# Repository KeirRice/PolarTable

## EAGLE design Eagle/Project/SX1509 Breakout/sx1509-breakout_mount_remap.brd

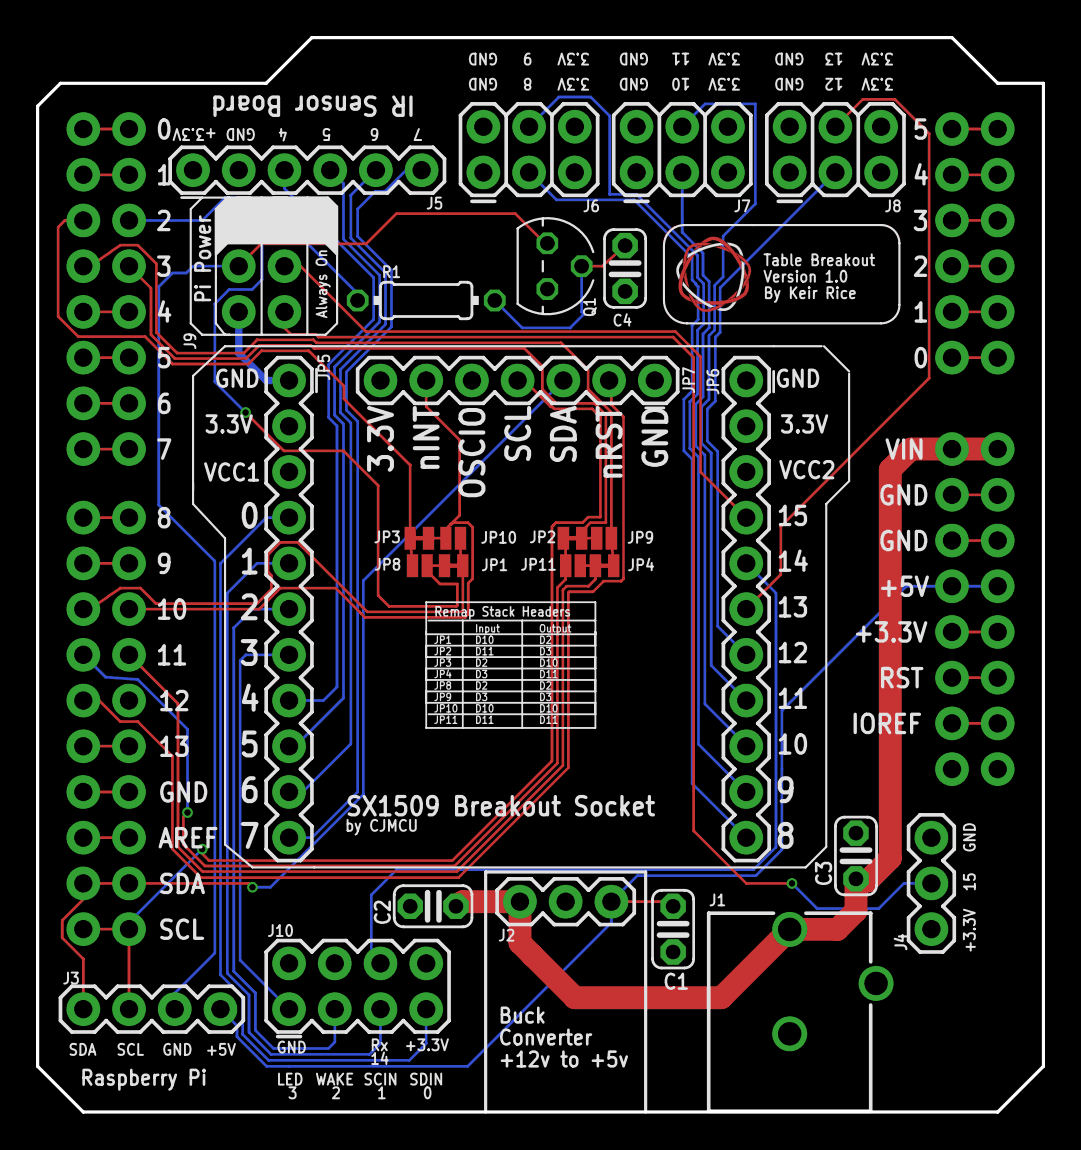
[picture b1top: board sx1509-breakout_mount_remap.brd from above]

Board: 2 copper layers, 55.9 x 59.7 mm, 30 parts (0 on the bottom side), 56 nets.

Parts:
B1: DownConnection; UNO_R3_SHIELD_NOLABELS
B2: UpConnection; UNO_R3_SHIELD_NOLABELS
C1, C2, C3, C4: 0.1uF; C025-024X044
J1: Pi Power Jack; POWER_JACK_PTH_BREAD
J2: 12V to 5V; 1X03
J3: Pi Connection; 1X04
J4: 1X03
J5: IR Sensors; 1X06
J6: Switch A + B; 2X3
J7: Switch C + D; 2X3
J8: Switch E + F; 2X3
J9: 2X3-NS
J10: LED + Radio; 2X4
JP1, JP2, JP3, JP4: SMT-JUMPER_2_NC_TRACE_NO-SILK
JP5, JP6: 1X11
JP7: 1X07
JP8, JP9, JP10, JP11: SMT-JUMPER_2_NO_NO-SILK
Q1: BC337; TO92
R1: 100; 0204/7
U$1: TRI_LOGO_5MM

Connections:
3.3V: B1.3.3V, B2.3.3V, J4.1, J5.1, J6.5, J6.6, J7.5, J7.6, J8.5, J8.6, J10.8, JP5.2, JP6.2, JP7.7
4: J5.3, JP5.8
5: J5.4, JP5.9
5V: B1.5V, B2.5V, C1.1, J2.3, J3.1
6: J5.5, JP5.10
7: J5.6, JP5.11
8: J6.3, JP6.11
9: J6.4, JP6.10
10: J7.3, JP6.9
11: J7.4, JP6.8
12: J8.3, JP6.7
12V: B1.VIN, B2.VIN, C2.2, C3.1, J1.PWR, J2.1
13: J8.4, JP6.6
15: J9.4, JP6.4
*D5: B1.D5, B2.D5
*D6: B1.D6, B2.D6
*D9: B1.D9, B2.D9
A0: B1.A0, B2.A0
A1: B1.A1, B2.A1
A2: B1.A2, B2.A2
A3: B1.A3, B2.A3
A4: B1.A4, B2.A4
A5: B1.A5, B2.A5
AREF: B1.AREF, B2.AREF
D4: B1.D4, B2.D4
D7: B1.D7, B2.D7
D8: B1.D8, B2.D8
D13: B1.D13, B2.D13
GND: C1.2, C2.1, C3.2, C4.2, J1.GND, J1.GNDBREAK, J2.2, J4.3, J5.2, J6.1, J6.2, J7.1, J7.2, J8.1, J8.2, J9.5, J10.2, JP5.1, JP6.1, JP7.1, Q1.1
GND@0: B1.GND@0, B2.GND@0
GND@1: B1.GND@1, B2.GND@1
GND@2: B1.GND@2, B2.GND@2
IOREF: B1.IOREF, B2.IOREF
unnamed: C4.1, Q1.2, R1.2
unnamed: J4.2, J9.6
unnamed: J9.2, R1.1
unnamed: B1.D2, JP3.2, JP8.2
unnamed: B1.D3, JP4.2, JP9.2
unnamed: B1.D10, JP1.2, JP10.2
unnamed: B1.D11, JP2.2, JP11.2
unnamed: B2.D2, JP1.1, JP8.1
unnamed: B2.D3, JP2.1, JP9.1
unnamed: B2.D11, JP4.1, JP11.1
NINT: B2.D10, JP3.1, JP7.6, JP10.1
NRESET: B1.D12, JP7.2
PI_GROUND: J3.2, J9.3, Q1.3
RES: B1.RES, B2.RES
RX: B1.RX, B2.RX
RXDATA: J10.6, JP6.5
SCIN: J10.5, JP5.5
SCL: B1.SCL, B2.SCL, J3.3, JP7.4
SDA: B1.SDA, B2.SDA, J3.4, JP7.3
SDIN: J10.7, JP5.4
TX: B1.TX, B2.TX
WAKE_LED: J10.1, JP5.7
WAKE_SW: J10.3, JP5.6

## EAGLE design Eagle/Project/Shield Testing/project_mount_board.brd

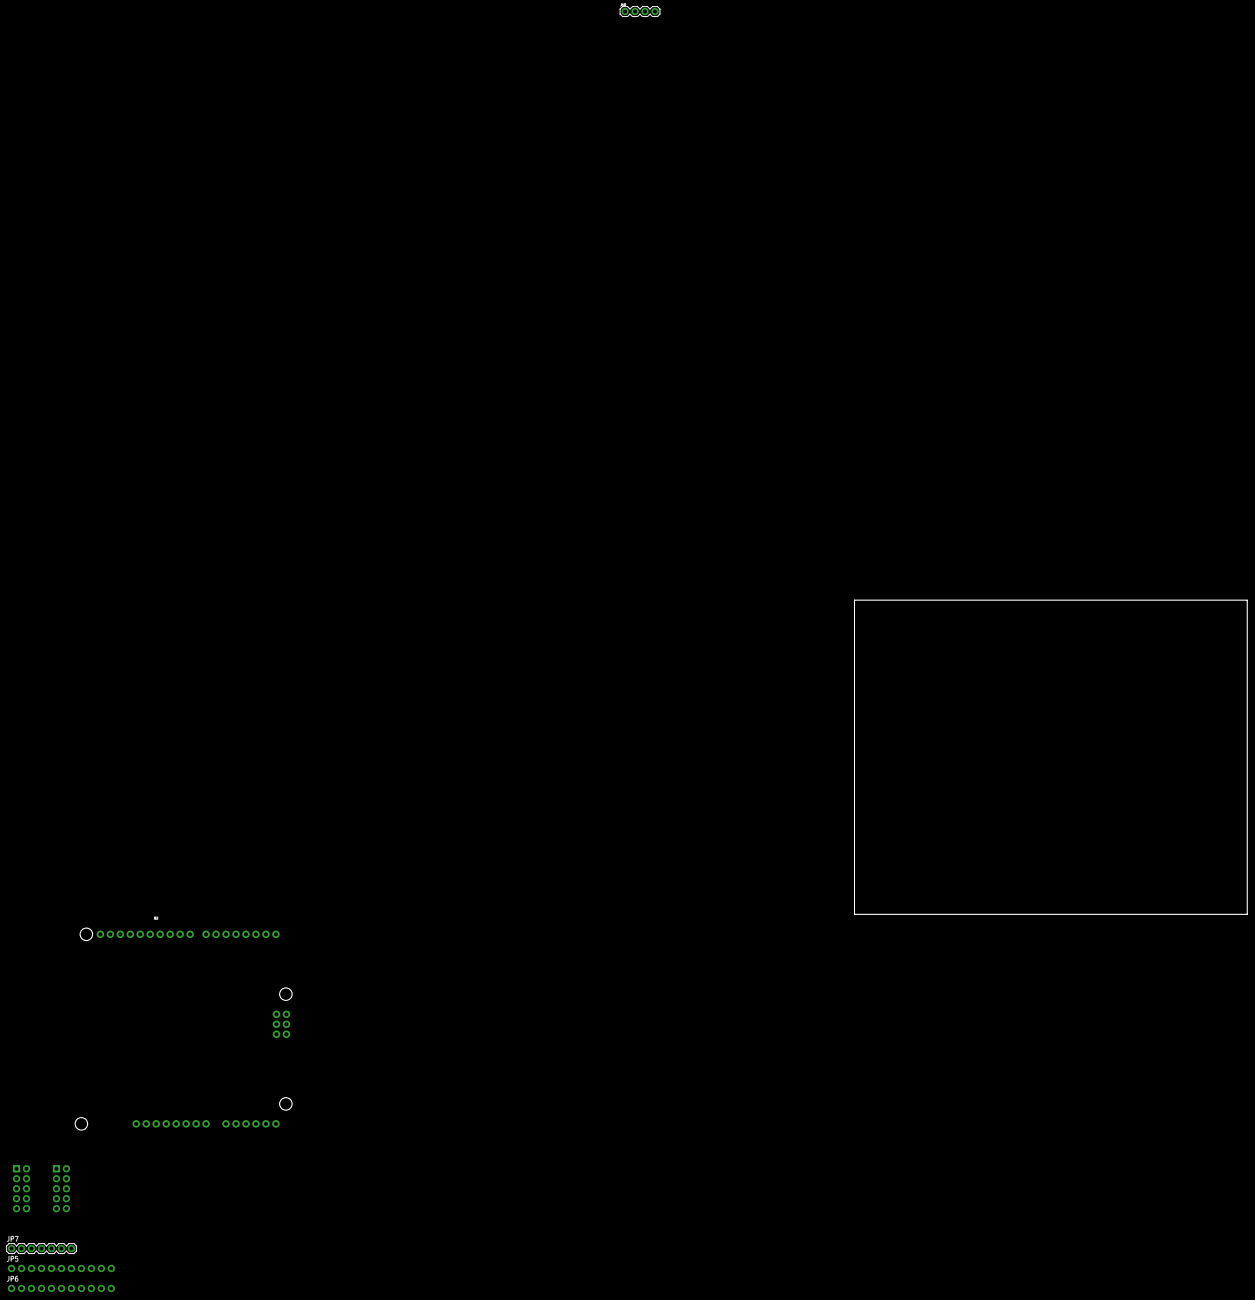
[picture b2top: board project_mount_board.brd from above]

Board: 2 copper layers, 100.0 x 80.0 mm, 7 parts (0 on the bottom side), 3 nets, no tracks yet.

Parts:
B2: ARDUINO_UNO_R3; ARDUINO_R3
J10: 1X04
JP1: IDC-5X2; 2X5-SHROUDED-NO_SILK
JP2: IDC-5x2; 2X5-SHROUDED-NO_SILK
JP5, JP6: 1X11_NO_SILK
JP7: 1X07

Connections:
5V: B2.5V, J10.4
GND: B2.GND@1, B2.GND@2, B2.GND@3, B2.GND@4, J10.1
RXDATA: B2.D12, J10.2

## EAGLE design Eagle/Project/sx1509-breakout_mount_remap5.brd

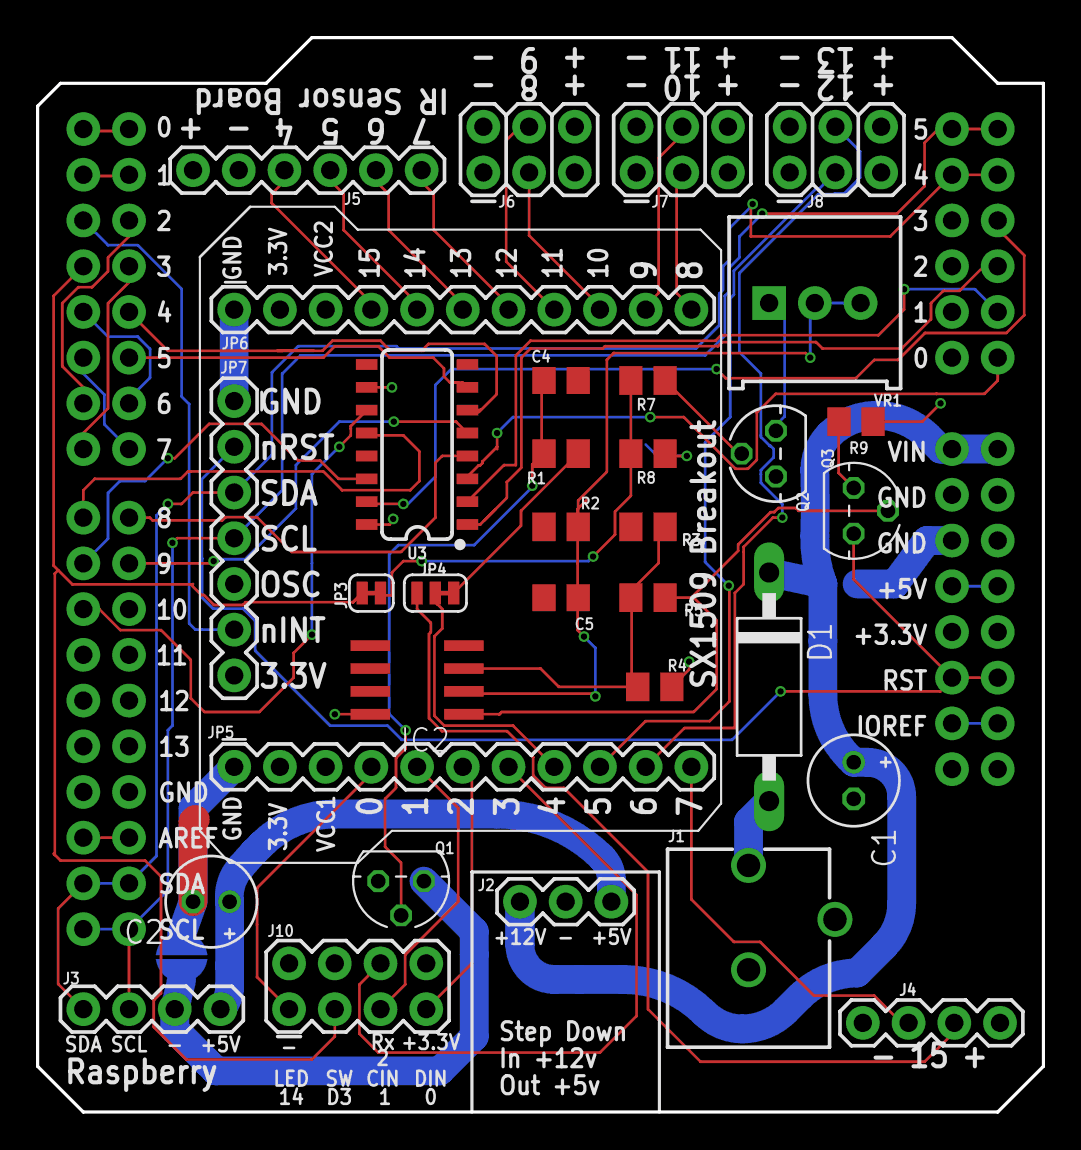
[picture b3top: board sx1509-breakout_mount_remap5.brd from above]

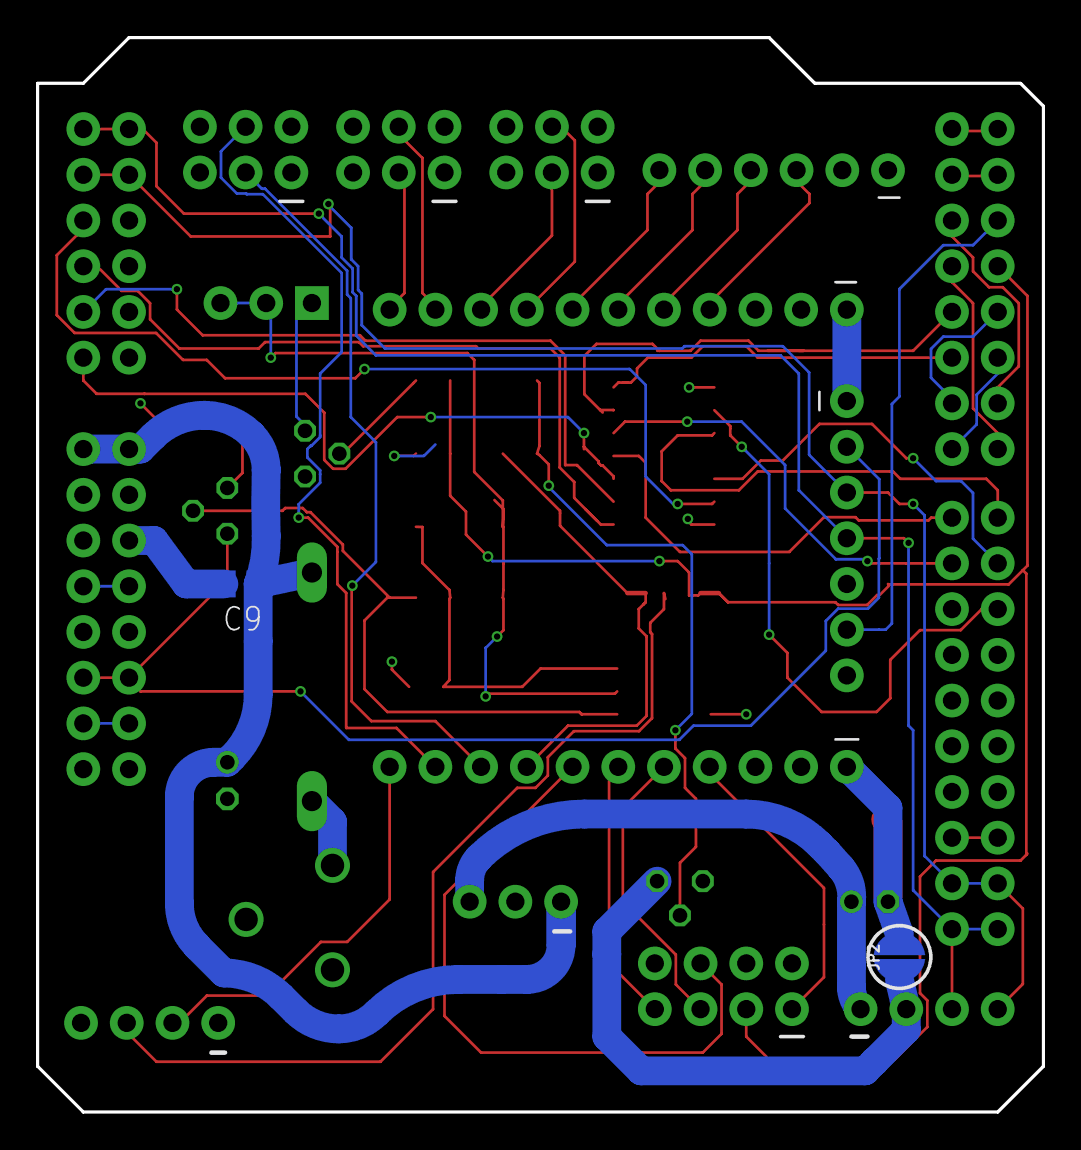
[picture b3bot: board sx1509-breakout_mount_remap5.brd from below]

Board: 2 copper layers, 55.9 x 59.7 mm, 38 parts (2 on the bottom side), 57 nets.

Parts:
B1: Connect down to Arduino; UNO_R3_SHIELD_NOLABELS
B2: Connect up to motor shield; UNO_R3_SHIELD_NOLABELS
C1, C2: 100u; E2-5
C4: 100nF; C0805
C5: 330uF; C0805
C9: 100n; C0805
D1: 1N5408; DO15-12
IC2: LM358D; SO08
J1: Pi Power Jack; POWER_JACK_PTH_BREAD
J2: Header - Right angled, female; 1X03
J3: Pi Connection; 1X04_1.24MM_RA_MALE
J4: extra points; 1X04_1.24MM_RA_MALE
J5: IR Sensors; 1X06
J6: Switch A + B; 2X3
J7: Switch C + D; 2X3
J8: Switch E + F; 2X3
J10: LED + Radio; 2X4
JP2: Bypass Power Control; SMT-JUMPER_2_NO_SILK_ROUND
JP3: Enable Hold to Reset; SMT-JUMPER_2_NC_TRACE_SILK
JP4: Route 15 to external; SMT-JUMPER_3_1-NC_TRACE_SILK
JP5: Left Sub-board Mount; 1X11
JP6: Right Sub-board Mount; 1X11
JP7: Top Sub-board Mount; 1X07
Q1: BC337; TO92
Q2: 2N3906; TO92D
Q3: BC547; TO92
R1, R7, R8, R9: 1k; M0805
R2: 22.1k; M0805
R3: 22k; M0805
R4: 16.2k; M0805
R5: 221k; M0805
U3: SN74HC595DR; SO16
U$2: TRI_LOGO_TOP_15MM
VR1: 10k; TRIMPOT-PTH-3386U

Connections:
3.3V: B1.3.3V, B2.3.3V, IC2.8, J4.1, J5.1, J6.5, J6.6, J7.5, J7.6, J8.5, J8.6, J10.8, JP5.2, JP6.2, JP7.7, Q2.E, R4.2, R8.1, R9.1, U3.10, U3.16
5V: B1.5V, B2.5V
12V: B1.VIN, B2.VIN, C1.+, C9.1, D1.C, J2.1
15_PLUG: J4.2, JP4.1
$N99: JP3.2, R7.2, R8.2
AREF: B1.AREF, B2.AREF
B0: J10.1, JP5.4
B1_SCIN: J10.5, JP5.5
B2_SDIN: J10.7, JP5.6
B3_RXDATA: J10.6, JP5.7
B4: JP4.2, JP5.8
B5: J8.3, JP5.9
B6: J8.4, JP5.10
B7: J4.3, JP5.11
B8: J7.3, JP6.11
B9: J7.4, JP6.10
B10: J6.3, JP6.9
B11: J6.4, JP6.8
B12: J5.6, JP6.7
B13: J5.5, JP6.6
B14: J5.4, JP6.5
B15: J5.3, JP6.4
CLK: B1.D10, U3.11
COMP_OUT: IC2.1, Q3.2, R5.1
DATA: B1.D9, U3.14
ENX: B2.A2, U3.1
ENY: B2.A0, U3.3
GND: B1.GND@0, B1.GND@1, B1.GND@2, B2.GND@0, B2.GND@1, B2.GND@2, C1.-, C2.-, C4.2, C5.2, C9.2, IC2.4, J1.GND, J1.GNDBREAK, J2.2, J4.4, J5.2, J6.1, J6.2, J7.1, J7.2, J8.1, J8.2, J10.2, JP2.2, JP5.1, JP6.1, JP7.1, Q1.1, R2.1, R3.1, U3.8, U3.13
IOREF: B1.IOREF, B2.IOREF
LATCH: B1.D8, U3.12
unnamed: Q2.B, R7.1
unnamed: C4.1, Q1.2, R1.2
unnamed: Q3.3, R9.2
unnamed: D1.A, J1.PWR
unnamed: IC2.3, R3.2, R4.1, R5.2
unnamed: Q2.C, VR1.1
unnamed: C5.1, IC2.2, R2.2, VR1.2, VR1.3
NINT: B1.D2, JP7.6
PIPOWER_SIGNAL: JP4.3, R1.1
PI_5V: C2.+, J2.3, J3.1
PI_GROUND: J3.2, JP2.1, Q1.3
RES: B1.RES, B2.RES, JP7.2, Q3.1
RX: B1.RX, B2.RX
SCL: B1.A5, B1.SCL, B2.A5, B2.SCL, J3.3, JP7.4
SDA: B1.A4, B1.SDA, B2.A4, B2.SDA, J3.4, JP7.3
SLEEPX: B2.A3, U3.15
SLEEPY: B2.A1, U3.2
TX: B1.TX, B2.TX
WAKE_SW: B1.D3, J10.3, JP3.1
XDIR: B1.D7, B2.D3
XMS1: B2.D4, U3.6
XMS2: B2.D5, U3.7
XSTEP: B1.D6, B2.D2
YDIR: B1.D5, B2.D7
YMS1: B2.D8, U3.4
YMS2: B2.D9, U3.5
YSTEP: B1.D4, B2.D6

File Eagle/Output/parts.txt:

Partlist

Exported from sx1509-breakout_mount_remap5.sch at 9/27/2018 1:54 PM

EAGLE Version 9.1.3 Copyright (c) 1988-2018 Autodesk, Inc.

Assembly variant: 

Part     Value                         Device                         Package                      Library                 Sheet

B1       Connect down to Arduino       ARDUINO_UNO_R3_SHIELDNOLABELS  UNO_R3_SHIELD_NOLABELS       keir_library            1
B2       Connect up to motor shield    ARDUINO_UNO_R3_SHIELDNOLABELS  UNO_R3_SHIELD_NOLABELS       keir_library            1
C1       100u                          CPOL-EUE2-5                    E2-5                         rcl                     1
C2       100u                          CPOL-EUE2-5                    E2-5                         rcl                     1
C4       100nF                         C-EUC0805                      C0805                        resistor                1
C5       330uF                         C-EUC0805                      C0805                        resistor                1
C9       100n                          C-EUC0805                      C0805                        rcl                     1
D1       1N5408                        1N5408                         DO15-12                      keir_library            1
IC2      LM358D                        LM358D                         SO08                         keir_library            1
J1       Pi Power Jack                 POWER_JACKPTH_BREAD            POWER_JACK_PTH_BREAD         SparkFun-Connectors     1
J2       Header - Right angled, female CONN_031X03_2.54MM_RA_FEMALE   1X03                         keir_library            1
J3       Pi Connection                 CONN_041X04_1.24MM_RA_MALE     1X04_1.24MM_RA_MALE          keir_library            1
J4                                     CONN_041X04_1.24MM_RA_MALE     1X04_1.24MM_RA_MALE          keir_library            1
J5       IR Sensors                    CONN_06SILK_FEMALE_PTH         1X06                         SparkFun-Connectors     1
J6       Switch A + B                  CONN_03X22X03_2.54MM_RA_MALE   2X3                          keir_library            1
J7       Switch C + D                  CONN_03X22X03_2.54MM_RA_MALE   2X3                          keir_library            1
J8       Switch E + F                  CONN_03X22X03_2.54MM_RA_MALE   2X3                          keir_library            1
J10      LED + Radio                   CONN_04X22X4_1.24MM_RA_MALE    2X4                          keir_library            1
JP2      Bypass Power Control          JUMPER-SMT_2_NO_SILK_ROUND     SMT-JUMPER_2_NO_SILK_ROUND   SparkFun-Jumpers        1
JP3      Enable Hold to Reset          JUMPER-SMT_2_NC_TRACE_SILK     SMT-JUMPER_2_NC_TRACE_SILK   SparkFun-Jumpers        1
JP4      Route 15 to external          JUMPER-SMT_3_1-NC_TRACE_SILK   SMT-JUMPER_3_1-NC_TRACE_SILK SparkFun-Jumpers        1
JP5                                    CONN_11                        1X11                         SparkFun-Connectors     1
JP6                                    CONN_11                        1X11                         SparkFun-Connectors     1
JP7                                    M07                            1X07                         SparkFun-Connectors     1
Q1       BC337                         BC337                          TO92                         transistor-npn          1
Q2       2N3906                        2N3906                         TO92D                        transistor-small-signal 1
Q3       BC547                         BC547                          TO92                         transistor-npn          1
R1       100                           R-US_R0805                     R0805                        resistor                1
R2       22.1k                         R-US_R0805                     R0805                        resistor                1
R3       22k                           R-US_R0805                     R0805                        resistor                1
R4       16.2k                         R-US_R0805                     R0805                        resistor                1
R5       221k                          R-US_R0805                     R0805                        resistor                1
R7       1k                            R-US_R0805                     R0805                        resistor                1
R8       1k                            R-US_R0805                     R0805                        resistor                1
R9       1k                            R-US_R0805                     R0805                        resistor                1
U3       SN74HC595DR                   SN74HC595HCD                   SO16                         keir_library            1
VR1      10k                           TRIMPOT-PTH-10MM-KNOB-1/2W-10% TRIMPOT-PTH-3386U            SparkFun-Resistors      1

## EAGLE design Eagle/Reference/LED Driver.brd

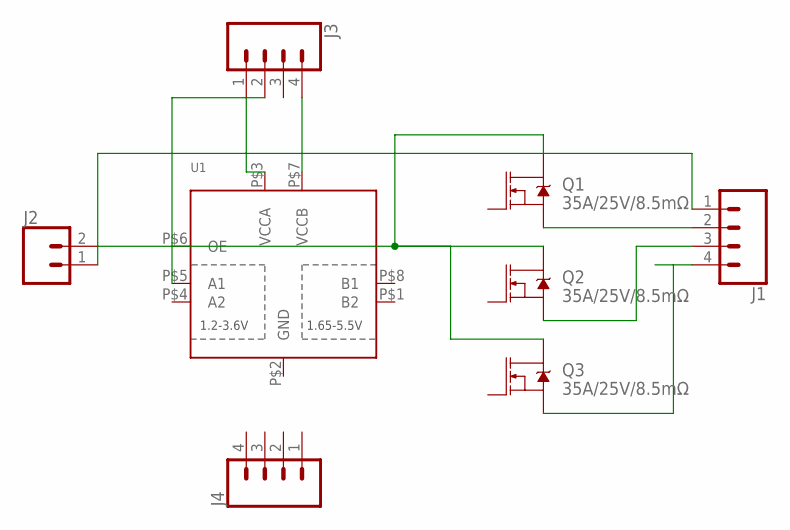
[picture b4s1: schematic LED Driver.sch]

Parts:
J1: CONN_04SCREW; SCREWTERMINAL-3.5MM-4
J2: CONN_023.5MM; SCREWTERMINAL-3.5MM-2
J3, J4: CONN_04JST-PTH; JST-4-PTH
Q1, Q2, Q3: 35A/25V/8.5mΩ; DPAK
U1: TXS0102; VFSOP-8

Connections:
unnamed: J2.2, Q1.4 (D), Q2.4 (D), Q3.4 (D)
unnamed: J1.2, Q1.3 (S)
unnamed: J1.3, Q2.3 (S)
unnamed: J1.4, Q3.3 (S)
unnamed: J1.1, J2.1
unnamed: J3.1, U1.P$3 (VCCA)
unnamed: J3.2, U1.P$5 (A1)
unnamed: J3.4, U1.P$7 (VCCB)

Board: 2 copper layers, 8 parts (0 on the bottom side), 8 nets, no tracks yet.

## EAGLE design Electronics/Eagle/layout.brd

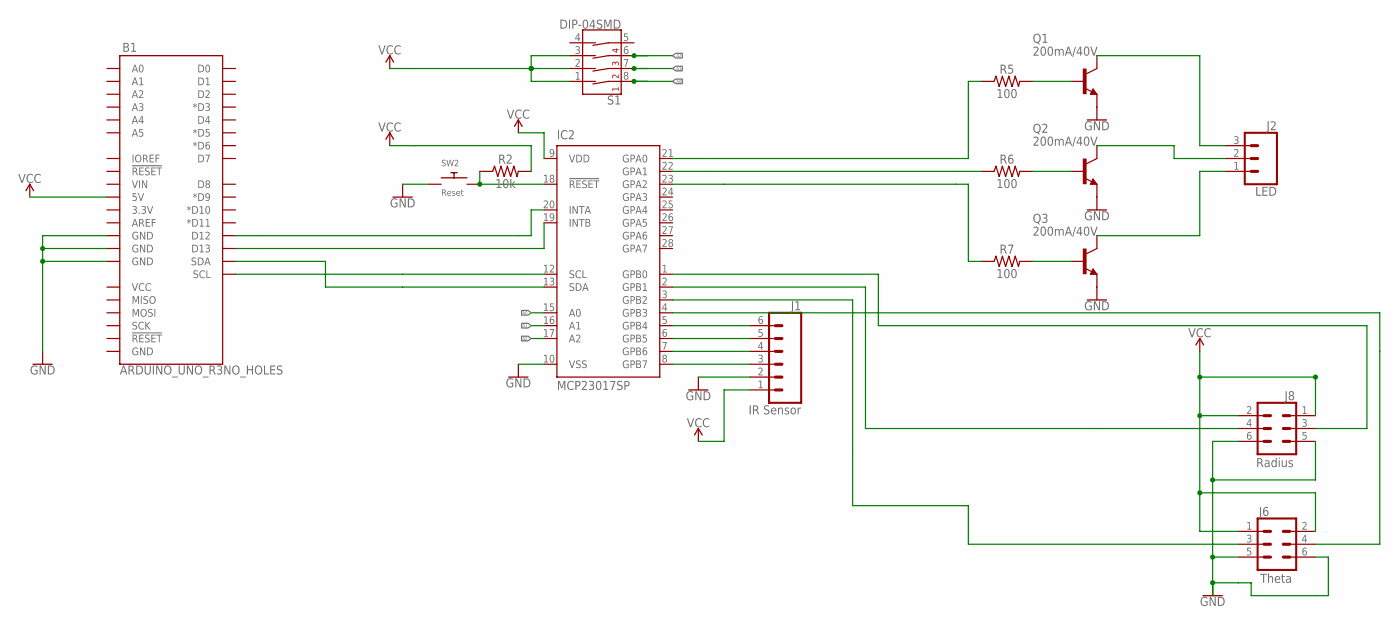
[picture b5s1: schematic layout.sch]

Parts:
B1: ARDUINO_UNO_R3NO_HOLES; ARDUINO_R3_NO_HOLES
IC2: MCP23017SP; DIL28-3
J1: IR Sensor; 1X06
J2: LED; 1X03
J6: Theta; 2X3
J8: Radius; 2X3
Q1, Q2, Q3: 200mA/40V; TO220
R2: 10k; 0603
R5, R6, R7: 100; 0603
S1: DIP-04SMD; DIPSWITCH-04-SMD
SW2: Reset; BTN_CK_KSS

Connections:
A0: IC2.15 (A0), S1.8 (1B)
A1: IC2.16 (A1), S1.7 (2B)
A2: IC2.17 (A2), S1.6 (3B)
B: IC2.23 (GPA2), R7.1
G: IC2.22 (GPA1), R6.1
GND: B1.GND@2 (GND), B1.GND@3 (GND), B1.GND@4 (GND), IC2.10 (VSS), J1.2, J6.5, J6.6, J8.5, J8.6, Q1.3 (E), Q2.3 (E), Q3.3 (E), SW2.P$1
INT_A: B1.D12, IC2.20 (INTA)
INT_B: B1.D13, IC2.19 (INTB)
IR_A: IC2.8 (GPB7), J1.3
IR_B: IC2.7 (GPB6), J1.4
IR_C: IC2.6 (GPB5), J1.5
IR_D: IC2.5 (GPB4), J1.6
unnamed: Q1.1 (B), R5.2
unnamed: Q2.1 (B), R6.2
unnamed: Q3.1 (B), R7.2
unnamed: J2.3, Q1.2 (C)
unnamed: J2.2, Q2.2 (C)
unnamed: J2.1, Q3.2 (C)
R: IC2.21 (GPA0), R5.1
RADIUS_A: IC2.1 (GPB0), J8.3
RADIUS_B: IC2.2 (GPB1), J8.4
RESET: IC2.18 (!RESET), R2.1, SW2.P$2
SDA: B1.SDA, IC2.13 (SDA)
SDL: B1.SCL, IC2.12 (SCL)
THETA_A: IC2.3 (GPB2), J6.3
THETA_B: IC2.4 (GPB3), J6.4
VCC: B1.5V, IC2.9 (VDD), J1.1, J6.1, J6.2, J8.1, J8.2, R2.2, S1.1 (1A), S1.2 (2A), S1.3 (3A)

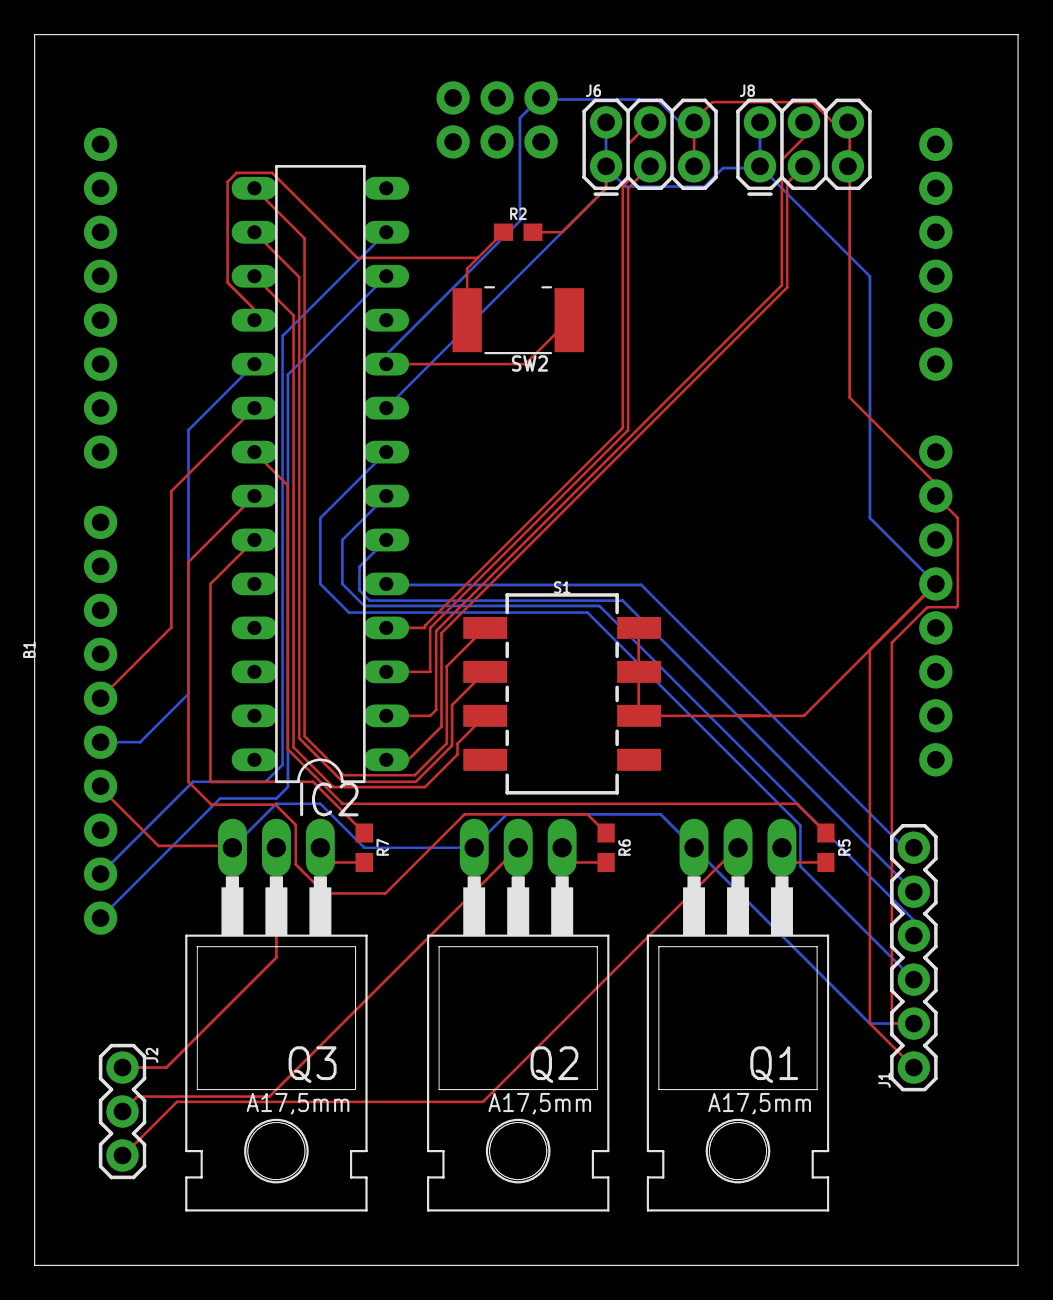
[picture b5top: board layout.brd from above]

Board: 2 copper layers, 56.8 x 71.1 mm, 15 parts (0 on the bottom side), 27 nets.

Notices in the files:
parts and their libraries:
SparkFun-Connectors: Licensing: Creative Commons ShareAlike 4.0 International - https://creativecommons.org/licenses/by-sa/4.0
SparkFun-Connectors: Licensing: CC v3.0 Share-Alike You are welcome to use this library for commercial purposes.
